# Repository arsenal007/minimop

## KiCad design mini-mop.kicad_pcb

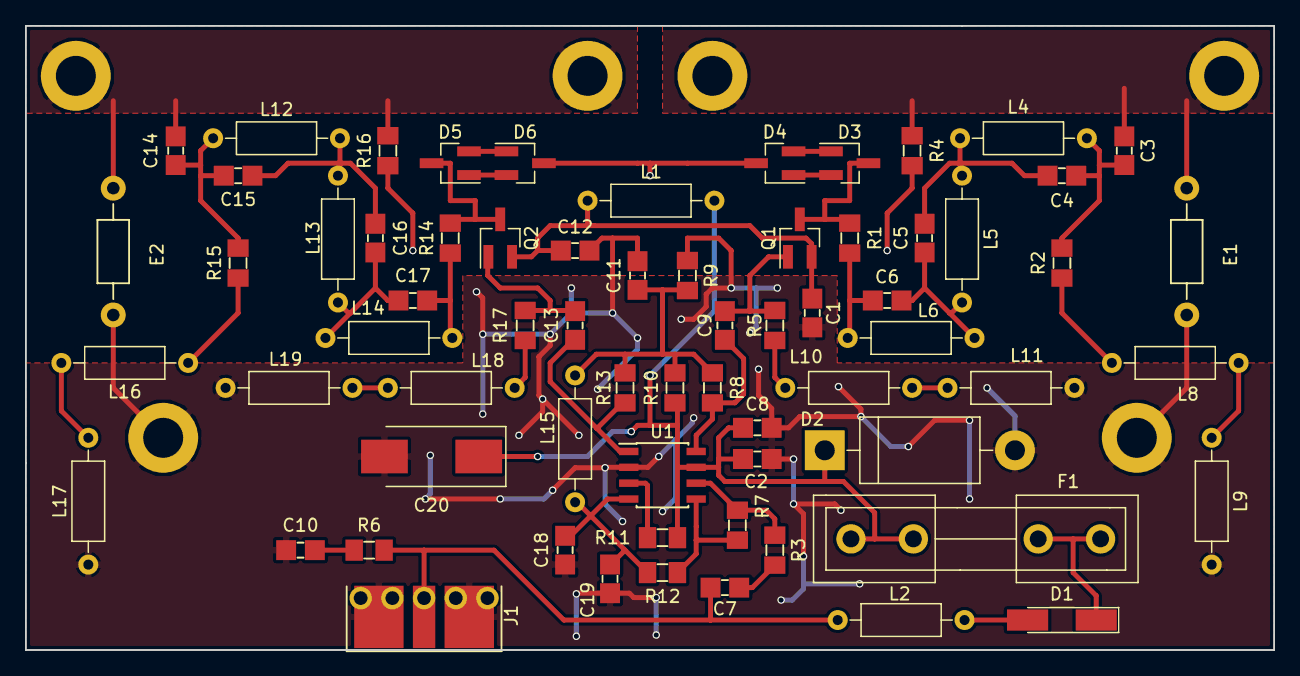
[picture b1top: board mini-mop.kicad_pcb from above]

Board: 2 copper layers, 100.0 x 50.0 mm, 73 parts (0 on the bottom side), 41 nets.

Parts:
AE1, AE2, AE3, AE4: Antenna; MountingHole_3.2mm_M3_DIN965_Pad
C1, C7, C8, C9, C10, C11, C12, C13, C19: 100n; C_1206_0603
C2, C18: 10n; C_1206_0603
C3, C14: 100; C_1206_0603
C4, C15: 1p; C_1206_0603
C5, C16: 1.8p; C_1206_0603
C6, C17: 2.2p; C_1206_0603
C20: 100uF; CP_Tantalum_Case-D_EIA-7343-31_Hand
D1: LL4148; D_MiniMELF_Handsoldering
D2: D_TVS; D_DO-201AD_P15.24mm_Horizontal
D3, D4, D5, D6: BAV99; SOT-23_Handsoldering
E1, E2: GAS; Resistor_Horizontal_RM10mm
F1: Fuse; Fuseholder5x20_horiz_open_inline_Type-I
J1: Conn_Coaxial; RFCONNECTOR
L1: 15uH; R_Axial_DIN0207_L6.3mm_D2.5mm_P10.16mm_Horizontal
L2: 4.7mH; R_Axial_DIN0207_L6.3mm_D2.5mm_P10.16mm_Horizontal
L4, L5, L12, L13: 1.8uH; R_Axial_DIN0207_L6.3mm_D2.5mm_P10.16mm_Horizontal
L6, L14: 3.3uH; R_Axial_DIN0207_L6.3mm_D2.5mm_P10.16mm_Horizontal
L8, L11, L15, L16, L19: 47uH; R_Axial_DIN0207_L6.3mm_D2.5mm_P10.16mm_Horizontal
L9, L17: 8.2mH; R_Axial_DIN0207_L6.3mm_D2.5mm_P10.16mm_Horizontal
L10, L18: 270uH; R_Axial_DIN0207_L6.3mm_D2.5mm_P10.16mm_Horizontal
P1, P2: Mount; MountingHole_3.2mm_M3_DIN965_Pad
Q1, Q2: BF862; SOT-23_Handsoldering
R1, R14: 680; R_1206_0603
R2, R8, R9, R10, R11, R13, R15: 10k; R_1206_0603
R3, R5, R6, R12, R17: 100; R_1206_0603
R4, R16: 1.5M; R_1206_0603
R7: 2k; R_1206_0603
U1: AD8129; SOIC-8_3.9x4.9mm_Pitch1.27mm

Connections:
GND: C1.2, C2.2, C8.2, C10.2, C11.2, C12.2, C18.1, C19.2, C20.2, D2.2, D4.3, D6.3, E1.2, E2.2, J1.2, L9.2, L11.1, L17.2, L19.1, P1.1, P2.1, R4.1, R9.1, R16.1, U1.2
unnamed: AE1.1, AE3.1, C3.1, E1.1, R4.2
unnamed: AE2.1, AE4.1, C14.1, E2.1, R16.2
unnamed: C1.1, C12.1, L1.1, Q1.2, Q2.2
unnamed: C2.1, C8.1, C20.1, D2.1, F1.2, L1.2, R10.1, R11.1, U1.7
unnamed: C3.2, C4.2, L4.1, R2.2
unnamed: C4.1, C5.2, L4.2, L5.1
unnamed: C5.1, C6.2, L5.2, L6.1
unnamed: C6.1, L6.2, R1.1
unnamed: C7.1, J1.1, L2.2, R6.1
unnamed: C7.2, R3.2
unnamed: C9.1, R8.1, U1.8
unnamed: C9.2, Q1.1, R5.1
unnamed: C10.1, R6.2
unnamed: C11.1, L15.1, R8.2, R9.2, R10.2, R13.1
unnamed: C13.1, R13.2, U1.1
unnamed: C13.2, Q2.1, R17.1
unnamed: C14.2, C15.2, L12.1, R15.2
unnamed: C15.1, C16.2, L12.2, L13.1
unnamed: C16.1, C17.2, L13.2, L14.1
unnamed: C17.1, L14.2, R14.1
unnamed: C18.2, C19.1, L15.2, R12.2, U1.4
unnamed: D1.1, F1.1
unnamed: D1.2, L2.1
unnamed: D3.1, D4.2
unnamed: D3.2, D4.1
unnamed: D3.3, Q1.3, R1.2
unnamed: D5.1, D6.2
unnamed: D5.2, D6.1
unnamed: D5.3, Q2.3, R14.2
unnamed: L8.1, R2.1
unnamed: L8.2, L9.1
unnamed: L10.1, L11.2
unnamed: L10.2, R5.2
unnamed: L16.1, R15.1
unnamed: L16.2, L17.1
unnamed: L18.1, L19.2
unnamed: L18.2, R17.2
unnamed: R3.1, R7.1, U1.6
unnamed: R11.2, U1.3
unnamed: R7.2, R12.1, U1.5

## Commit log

2019-03-16 schematics elements bugs correction
